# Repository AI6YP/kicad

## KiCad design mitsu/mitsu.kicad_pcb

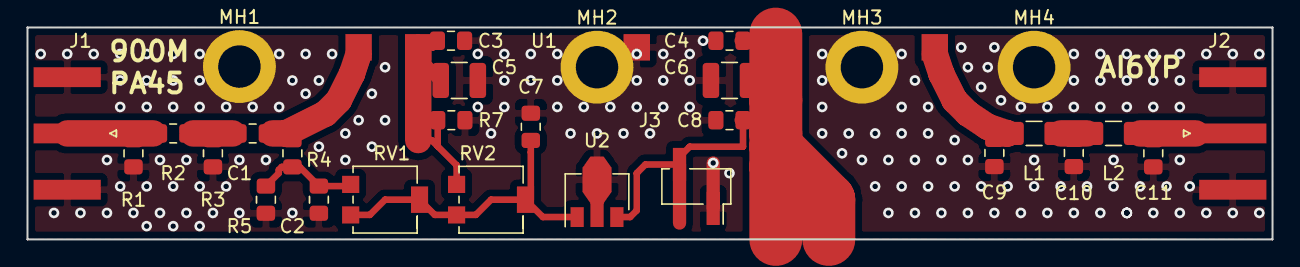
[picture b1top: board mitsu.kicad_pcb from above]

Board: 2 copper layers, 94.0 x 16.0 mm, 30 parts (0 on the bottom side), 11 nets.

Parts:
C1: 1000; C_0805_2012Metric_Pad1.15x1.40mm_HandSolder
C2, C3, C4: 4700; C_0805_2012Metric_Pad1.15x1.40mm_HandSolder
C5, C6: 22.0; C_1210_3225Metric
C7, C8: 0.1; C_0805_2012Metric_Pad1.15x1.40mm_HandSolder
C9, C11: 4.7; C_0805_2012Metric_Pad1.15x1.40mm_HandSolder
C10: 7.5; C_0805_2012Metric_Pad1.15x1.40mm_HandSolder
J1, J2: Conn_Coaxial; SMA_Amphenol_132289_EdgeMount
J3: Conn_01x04_Male; PinHeader_1x02_P2.54mm_Vertical_SMD_Pin1Right
L1, L2: 11u; L_1206_3216Metric
MH1, MH2, MH3, MH4: MountingHole; MountingHole_3.2mm_M3_ISO14580_Pad
R1, R3: 300; R_0805_2012Metric_Pad1.15x1.40mm_HandSolder
R2: 18; R_0805_2012Metric_Pad1.15x1.40mm_HandSolder
R4: 15k; R_0805_2012Metric_Pad1.15x1.40mm_HandSolder
R5, R7: 470; R_0805_2012Metric_Pad1.15x1.40mm_HandSolder
RV1, RV2: 500; Potentiometer_Bourns_3214G_Horizontal
U1: MPA
U2: L78L06_SOT89; SOT-89-3

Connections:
+12V: C4.2, C6.2, C8.1, J3.2, U1.3, U2.3
GNDPWR: C2.2, C3.2, C4.1, C5.2, C6.1, C7.2, C8.2, C9.1, C10.1, C11.1, J1.2, J2.2, J3.1, MH1.1, MH2.1, MH3.1, MH4.1, R1.2, R3.2, R5.1, R7.2, U1.5, U2.2
unnamed: C1.1, R4.1, U1.1
unnamed: C1.2, R2.1, R3.1
unnamed: C2.1, R4.2, R5.2, RV1.3
unnamed: C3.1, C5.1, R7.1, RV2.3, U1.2
unnamed: C7.1, RV1.1, RV1.2, RV2.1, RV2.2, U2.1
unnamed: C9.2, L1.1, U1.4
unnamed: C10.2, L1.2, L2.1
unnamed: C11.2, J2.1, L2.2
unnamed: J1.1, R1.1, R2.2

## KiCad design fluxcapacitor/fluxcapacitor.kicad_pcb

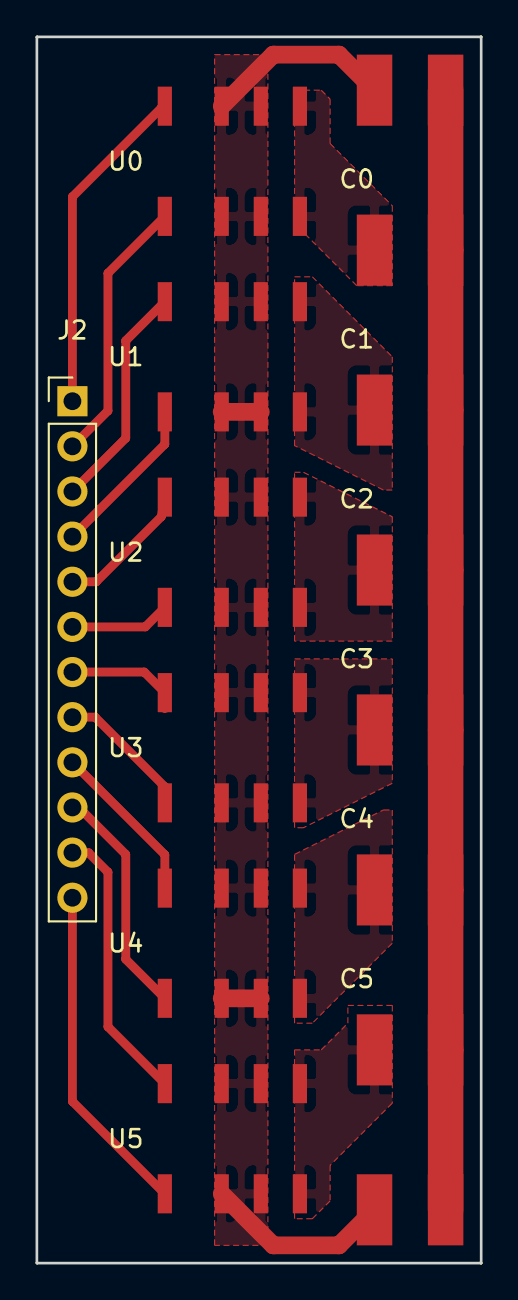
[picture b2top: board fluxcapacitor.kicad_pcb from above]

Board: 2 copper layers, 25.0 x 69.0 mm, 15 parts (0 on the bottom side), 20 nets.

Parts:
C0, C1, C2, C3, C4, C5, C100, C101: C; C_1111
J2: Conn_01x12; Pin_Header_Straight_1x12_Pitch2.54mm
U0, U1, U2, U3, U4, U5: IM_Relay_Bis; IM_Relay_Gul_Wings

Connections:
B: C100.2, C101.2, U0.2, U0.3, U0.6, U0.7, U1.2, U1.3, U1.6, U1.7, U2.2, U2.3, U2.6, U2.7, U3.2, U3.3, U3.6, U3.7, U4.2, U4.3, U4.6, U4.7, U5.2, U5.3, U5.6, U5.7
unnamed: C0.1, C1.1, C2.1, C3.1, C4.1, C5.1, C100.1, C101.1
unnamed: C0.2, U0.4, U0.5
unnamed: C1.2, U1.4, U1.5
unnamed: C2.2, U2.4, U2.5
unnamed: C3.2, U3.4, U3.5
unnamed: C4.2, U4.4, U4.5
unnamed: C5.2, U5.4, U5.5
unnamed: J2.1, U0.8
unnamed: J2.2, U0.1
unnamed: J2.3, U1.8
unnamed: J2.4, U1.1
unnamed: J2.5, U2.8
unnamed: J2.6, U2.1
unnamed: J2.7, U3.8
unnamed: J2.8, U3.1
unnamed: J2.9, U4.8
unnamed: J2.10, U4.1
unnamed: J2.11, U5.8
unnamed: J2.12, U5.1

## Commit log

2017-10-12 initial inductor model
2017-10-12 toroid color fix
2017-10-12 added stl, amf version
2017-10-14 added linear coil example
2017-10-14 updated coil + STL
2017-10-14 added X3D version of coil
2017-10-15 added winded toroid coil model
2017-10-18 L pcb svg update
2017-10-18 L16 v1
2017-10-18 git ignore
2017-10-18 initial package
2017-10-19 added flux capacitor v1
2017-10-25 moved 3d models into tokamak folder
2017-10-25 moved 3d model of coil into tokamak folder
2018-01-02 added helix code
2018-01-02 updated license years
2018-01-04 helix improvements
2018-01-07 915MHz version
2018-01-15 new version of helix
2018-01-15 fixed helix5
2018-01-15 updated helix generator to fix shapeways issues
2018-01-15 added external parameters
2018-02-26 added more openjscad elements
2018-03-05 more filters
2018-03-08 initial helix board
2018-03-22 more gravitsapas
2018-04-28 new version of helical
2018-04-28 started 3 stage filter
2018-04-30 new version of helix filter
2018-09-18 added mitsubishi board
2018-09-18 fixed PA footprint
2018-09-20 v1.0
2018-10-19 helix v6
2018-10-19 final changes for mitsu v1
2019-01-06 v1 fixes
2022-09-01 xpoho poc
2022-09-01 more packages to use
2023-12-23 EMI shield
2024-01-08 initial components for Kicad 7 library
2024-01-08 happy new year
2024-06-18 update components
2025-01-01 TV frame 3D model
2025-06-15 current state of library
2025-06-15 cleanup
2025-06-18 added AS179
2025-06-18 added YP3035W
2025-06-18 added 74LVC2G14, YP3035W, LP2985
2025-07-13 add 3D QFN/DFN generator
